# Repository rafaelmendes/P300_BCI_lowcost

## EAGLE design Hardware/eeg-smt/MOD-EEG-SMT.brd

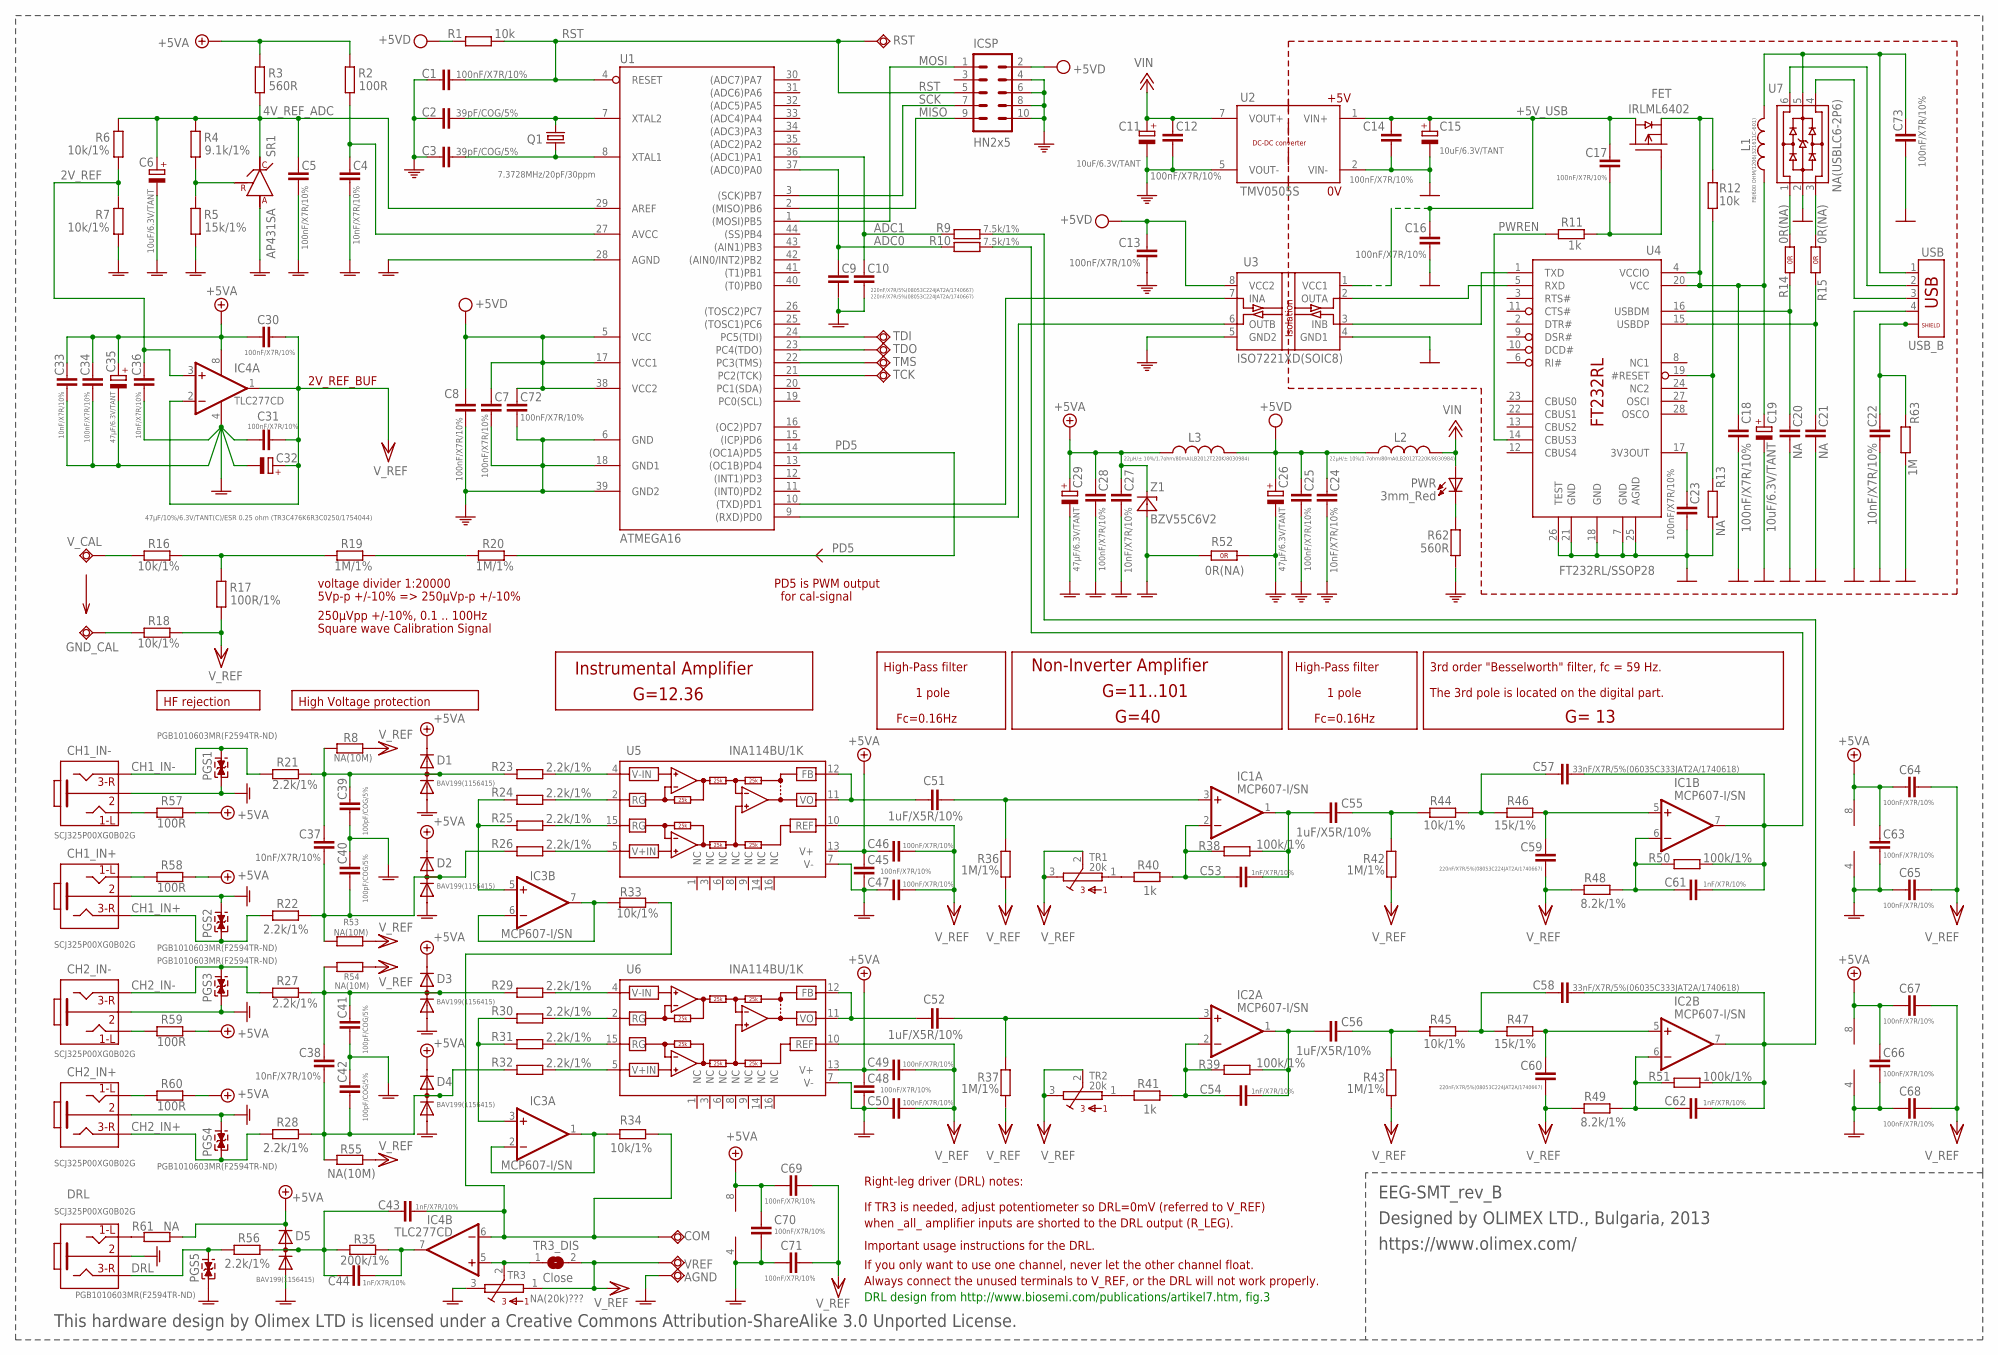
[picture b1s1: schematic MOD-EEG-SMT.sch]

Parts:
AGND: TESTPAD3; TEST_PAD40/70/SQUARE
C1, C5, C7, C8, C12, C13, C14, C16, C17, C18, C23, C25, C28, C30, C31, C34, C45, C46, C47, C48, C49, C50, C63, C64, C65, C66, C67, C68, C69, C70, C71, C72, C73: 100nF/X7R/10%; C0603_DWS
C2, C3: 39pF/COG/5%; C0603_DWS
C4, C22, C24, C27, C33, C36, C37, C38: 10nF/X7R/10%; C0603_DWS
C6, C11, C15, C19: 10uF/6.3V/TANT; CT3216
C9, C10, C59, C60: 220nF/X7R/5%(08053C224JAT2A/1740667); C0805_5MIL_DWS
C20, C21: NA; C0603_DWS_NA
C26, C29, C35: 47µF/6.3V/TANT; CT3528
C32: 47µF/10%/6.3V/TANT(C)/ESR 0.25 ohm (TR3C476K6R3C0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; CT6032
C39, C40, C41, C42: 100pF/COG/5%; C0603_DWS
C43, C44, C53, C54, C61, C62: 1nF/X7R/10%; C0603_DWS
C51, C52, C55, C56: 1uF/X5R/10%; C0603_DWS
C57, C58: 33nF/X7R/5%(06035C333JAT2A/1740618); C0603_DWS
CH1_IN+, CH1_IN-, CH2_IN+, CH2_IN-: SCJ325P00XG0B02G; PHONE_JACK-SMD
COM: TESTPAD3; TEST_PAD40/70/SQUARE
D1, D2, D3, D4, D5: BAV199(1156415); SOT23C(BAT54S)
DRL: SCJ325P00XG0B02G; PHONE_JACK-SMD
FET: IRLML6402; SOT23
GND_CAL: TESTPAD3; TEST_PAD40/70/SQUARE
IC1, IC2, IC3: MCP607-I/SN; SO08
IC4: TLC277CD; SO08
ICSP: HN2x5; ML10_NEW
L1: FB/600 OHM/1206(321611C-601); L1206_5MIL
L2, L3: 22µH/± 10%/1.7ohm/80mA(LB2012T220K/8030984); L0805_5MIL_DWS
PGS1, PGS2, PGS3, PGS4, PGS5: PGB1010603MR(F2594TR-ND); 0603
PWR: 3mm_Red; LED-3.0MM
Q1: 7.3728MHz/20pF/30ppm; HC49/SMD2_THIN
R1, R12: 10k; R0603_5MIL_DWS
R2, R57, R58, R59, R60: 100R; R0603_5MIL_DWS
R3, R62: 560R; R0603_5MIL_DWS
R4: 9.1k/1%; R0603_5MIL_DWS
R5, R46, R47: 15k/1%; R0603_5MIL_DWS
R6, R7, R16, R18, R33, R34, R44, R45: 10k/1%; R0603_5MIL_DWS
R8, R53, R54, R55: NA(10M); R0603_5MIL_DWS
R9, R10: 7.5k/1%; R0603_5MIL_DWS
R11, R40, R41: 1k; R0603_5MIL_DWS
R13, R61: NA; R0603_5MIL_DWS_NA
R14, R15, R52: 0R(NA); 0603_0R
R17: 100R/1%; R0603_5MIL_DWS
R19, R20, R36, R37, R42, R43: 1M/1%; R0603_5MIL_DWS
R21, R22, R23, R24, R25, R26, R27, R28, R29, R30, R31, R32, R56: 2.2k/1%; R0603_5MIL_DWS
R35: 200k/1%; R0603_5MIL_DWS
R38, R39, R50, R51: 100k/1%; R0603_5MIL_DWS
R48, R49: 8.2k/1%; R0603_5MIL_DWS
R63: 1M; R0603_5MIL_DWS
RST: TESTPAD80/30; SMD80/30
SR1: AP431SA; SOT-23
TCK: TESTPAD80/30; SMD80/30
TDI: TESTPAD80/30; SMD80/30
TDO: TESTPAD80/30; SMD80/30
TMS: TESTPAD80/30; SMD80/30
TR1, TR2: 20k; S64Y
TR3: NA(20k)???; S64Y
TR3_DIS: Close; SJ_1_SMALLER
U1: ATMEGA16; 44TQFP
U2: TMV0505S; TMADCDC
U3: ISO7221XD(SOIC8); SO-8_ISOLATE
U4: FT232RL/SSOP28; SSOP28
U5, U6: INA114BU/1K; SO16
U7: NA(USBLC6-2P6); USBLC6-2P6
USB: USB_B; USB_NEAR_BLACK
VREF: TESTPAD3; TEST_PAD40/70/SQUARE
V_CAL: TESTPAD3; TEST_PAD40/70/SQUARE
Z1: BZV55C6V2; MINI-MELF

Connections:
2V_REF: C36.1, IC4.3 (+IN), R6.1, R7.2
4V_REF_ADC: C5.1, C6.+, R3.1, R4.2, R6.2, SR1.1 (C), U1.29 (AREF)
+5V: C27.1, C28.1, C29.+, C30.2, C33.1, C34.1, C35.+, C45.1, C46.1, C48.1, C49.1, C63.1, C64.1, C66.1, C67.1, C69.1, C70.1, D1.2 (K), D2.2 (K), D3.2 (K), D4.2 (K), D5.2 (K), IC1.8 (V+), IC2.8 (V+), IC3.8 (V+), IC4.8 (V+), L3.2, R2.2, R3.2, R57.2, R58.2, R59.2, R60.2, R61.2, U5.13 (V+), U6.13 (V+), Z1.1 (C)
+5V_USB: C14.1, C15.+, C16.1, C17.1, FET.3 (D), U2.1 (VIN+), U3.1 (VCC1)
+12V: C11.+, C12.1, L2.1, PWR.A, U2.7 (VOUT+)
ADC0: C9.1, R10.1, U1.37 ((ADC0)PA0)
ADC1: C10.1, R9.1, U1.36 ((ADC1)PA1)
CH1_IN+: CH1_IN+.2 (3), PGS2.1, R22.1
CH1_IN-: CH1_IN-.2 (3), PGS1.2, R21.1
CH2_IN+: CH2_IN+.2 (3), PGS4.1, R28.1
CH2_IN-: CH2_IN-.2 (3), PGS3.2, R27.1
DRL: DRL.2 (3), PGS5.2, R56.1
GND: C14.2, C15.-, C16.2, C18.2, C19.-, C20.2, C21.2, C22.2, C23.2, C73.2, R13.1, R63.1, U2.2 (VIN-), U3.4 (GND1), U4.7 (GND), U4.18 (GND), U4.21 (GND), U4.25 (AGND), U4.26 (TEST), U7.2, USB.4
GNDA: AGND.P$1, C4.2, C5.2, C6.-, C9.2, C10.2, C27.2, C28.2, C29.-, C31.2, C32.-, C33.2, C34.2, C35.-, C36.2, C39.1, C40.2, C41.1, C42.2, C45.2, C47.1, C48.2, C50.1, C63.2, C65.1, C66.2, C68.1, C70.2, C71.1, CH1_IN+.1 (2), CH1_IN-.1 (2), CH2_IN+.1 (2), CH2_IN-.1 (2), D1.1 (A), D2.1 (A), D3.1 (A), D4.1 (A), D5.1 (A), DRL.1 (2), IC1.4 (V-), IC2.4 (V-), IC3.4 (V-), IC4.4 (V-), PGS1.1, PGS2.2, PGS3.1, PGS4.2, PGS5.1, R5.1, R7.1, R52.1 (1.1), SR1.3 (A), TR3.3, U1.28 (AGND), U5.7 (V-), U6.7 (V-), Z1.2 (A)
MISO: ICSP.9, U1.2 ((MISO)PB6)
MOSI: ICSP.1, U1.1 ((MOSI)PB5)
unnamed: R14.1 (1.1), U7.1
unnamed: R15.1 (1.1), U7.3
unnamed: TDI.P$1, U1.24 (PC5(TDI))
unnamed: TDO.P$1, U1.23 (PC4(TDO))
unnamed: TMS.P$1, U1.22 (PC3(TMS))
unnamed: TCK.P$1, U1.21 (PC2(TCK))
unnamed: CH1_IN-.5 (1), R57.1
unnamed: CH1_IN+.5 (1), R58.1
unnamed: C43.2, C44.2, D5.3 (AK), R35.1, R56.2
unnamed: CH2_IN+.5 (1), R60.1
unnamed: CH2_IN-.5 (1), R59.1
unnamed: DRL.5 (1), R61.1
unnamed: PWR.K (C), R62.2
unnamed: U3.2 (OUTA), U4.5 (RXD)
unnamed: C22.1, R63.2, USB.P$1 (5), USB.P$2 (6)
unnamed: U7.6, USB.2
unnamed: U3.3 (INB), U4.1 (TXD)
unnamed: C4.1, R2.1, U1.27 (AVCC)
unnamed: R4.1, R5.2, SR1.2 (R)
unnamed: U1.10 ((TXD)PD1), U3.7 (INA)
unnamed: U1.9 ((RXD)PD0), U3.6 (OUTB)
unnamed: U7.4, USB.3
unnamed: C73.1, L1.1, U7.5, USB.1
unnamed: C3.1, Q1.2, U1.8 (XTAL1)
unnamed: C2.1, Q1.1, U1.7 (XTAL2)
unnamed: R40.2, TR1.1
unnamed: R41.2, TR2.1
unnamed: R12.1, R13.2, U4.19 (#RESET)
unnamed: C23.1, U4.17 (3V3OUT)
unnamed: C18.1, C19.+, FET.2 (S), L1.2, R12.2, U4.4 (VCCIO), U4.20 (VCC)
unnamed: C55.2, R42.1, R44.1
unnamed: C51.1, U5.11 (VO), U5.12 (FB)
unnamed: R23.1, U5.4 (V-IN)
unnamed: R24.1, U5.2 (RG)
unnamed: C37.1, C40.1, D2.3 (AK), R22.2, R26.2, R53.2
unnamed: C37.2, C39.2, D1.3 (AK), R8.2, R21.2, R23.2
unnamed: C38.1, C42.1, D4.3 (AK), R28.2, R32.2, R55.2
unnamed: C38.2, C41.2, D3.3 (AK), R27.2, R29.2, R54.2
unnamed: R25.1, U5.15 (RG)
unnamed: C51.2, IC1.3 (+IN), R36.1
unnamed: IC3.5 (+IN), R24.2, R25.2
unnamed: C53.2, C55.1, IC1.1 (OUT), R38.2
unnamed: C53.1, IC1.2 (-IN), R38.1, R40.1
unnamed: R26.1, U5.5 (V+IN)
unnamed: C59.1, IC1.5 (+IN), R46.2
unnamed: C57.1, R44.2, R46.1
unnamed: C57.2, C61.2, IC1.7 (OUT), R10.2, R50.2
unnamed: C61.1, IC1.6 (-IN), R48.1, R50.1
unnamed: C52.2, IC2.3 (+IN), R37.1
unnamed: C54.2, C56.1, IC2.1 (OUT), R39.2
unnamed: C54.1, IC2.2 (-IN), R39.1, R41.1
unnamed: C60.1, IC2.5 (+IN), R47.2
unnamed: C58.1, R45.2, R47.1
unnamed: C58.2, C62.2, IC2.7 (OUT), R9.2, R51.2
unnamed: C62.1, IC2.6 (-IN), R49.1, R51.1
unnamed: C56.2, R43.1, R45.1
unnamed: C52.1, U6.11 (VO), U6.12 (FB)
unnamed: R30.1, U6.2 (RG)
unnamed: R31.1, U6.15 (RG)
unnamed: IC3.3 (+IN), R30.2, R31.2
unnamed: R29.1, U6.4 (V-IN)
unnamed: R32.1, U6.5 (V+IN)
unnamed: IC3.1 (OUT), IC3.2 (-IN), R34.2
unnamed: IC3.6 (-IN), IC3.7 (OUT), R33.2
unnamed: IC4.5 (+IN), TR3.2, TR3_DIS.1
unnamed: C44.1, IC4.7 (OUT), R35.2
unnamed: R19.2, R20.1
unnamed: C43.1, COM.P$1, IC4.6 (-IN), R33.1, R34.1
unnamed: R16.2, R17.2, R19.1
unnamed: R16.1, V_CAL.P$1
unnamed: GND_CAL.P$1, R18.1
unnamed: C17.2, FET.1 (G), R11.2
PD5: R20.2, U1.14 ((OC1A)PD5)
PE: C1.2, C2.2, C3.2, C7.2, C8.2, C11.-, C12.2, C13.2, C24.2, C25.2, C26.-, C72.2, ICSP.4, ICSP.6, ICSP.8, ICSP.10, R52.2 (1.2), R62.1, U1.6 (GND), U1.18 (GND1), U1.39 (GND2), U2.5 (VOUT-), U3.5 (GND2)
PWREN: R11.1, U4.14 (CBUS3)
RST: C1.1, ICSP.5, R1.2, RST.P$1, U1.4 (RESET)
SCK: ICSP.7, U1.3 ((SCK)PB7)
USBDM: C20.1, R14.2 (1.2), U4.16 (USBDM)
USBDP: C21.1, R15.2 (1.2), U4.15 (USBDP)
VCC/2: C30.1, C31.1, C32.+, C46.2, C47.2, C49.2, C50.2, C59.2, C60.2, C64.2, C65.2, C67.2, C68.2, C69.2, C71.2, IC4.1 (OUT), IC4.2 (-IN), R8.1, R17.1, R18.2, R36.2, R37.2, R42.2, R43.2, R48.2, R49.2, R53.1, R54.1, R55.1, TR1.2, TR1.3, TR2.2, TR2.3, TR3.1, TR3_DIS.2, U5.10 (REF), U6.10 (REF), VREF.P$1
VPP: C7.1, C8.1, C13.1, C24.1, C25.1, C26.+, C72.1, ICSP.2, L2.2, L3.1, R1.1, U1.5 (VCC), U1.17 (VCC1), U1.38 (VCC2), U3.8 (VCC2)

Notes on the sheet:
PD5 is PWM output
for cal-signal
250µVpp +/-10%, 0.1 .. 100Hz
Square wave Calibration Signal
voltage divider 1:20000
G=40
G=11..101
5Vp-p +/-10% => 250µVp-p +/-10%
3rd order "Besselworth" filter, fc = 59 Hz.
The 3rd pole is located on the digital part.
Fc=0.16Hz
HF rejection
High Voltage protection
High-Pass filter
Non-Inverter Amplifier
G= 13
1 pole
G=12.36
2V_REF_BUF
Instrumental Amplifier
DRL design from http://www.biosemi.com/publications/artikel7.htm, fig.3
If TR3 is needed, adjust potentiometer so DRL=0mV (referred to V_REF)
when _all_ amplifier inputs are shorted to the DRL output (R_LEG).
If you only want to use one channel, never let the other channel float.
Important usage instructions for the DRL.
Always connect the unused terminals to V_REF, or the DRL will not work properly.
Right-leg driver (DRL) notes:
+5V
This hardware design by Olimex LTD is licensed under a Creative Commons Attribution-ShareAlike 3.0 Unported License.
Designed by OLIMEX LTD., Bulgaria, 2013
https://www.olimex.com/
EEG-SMT_rev_B

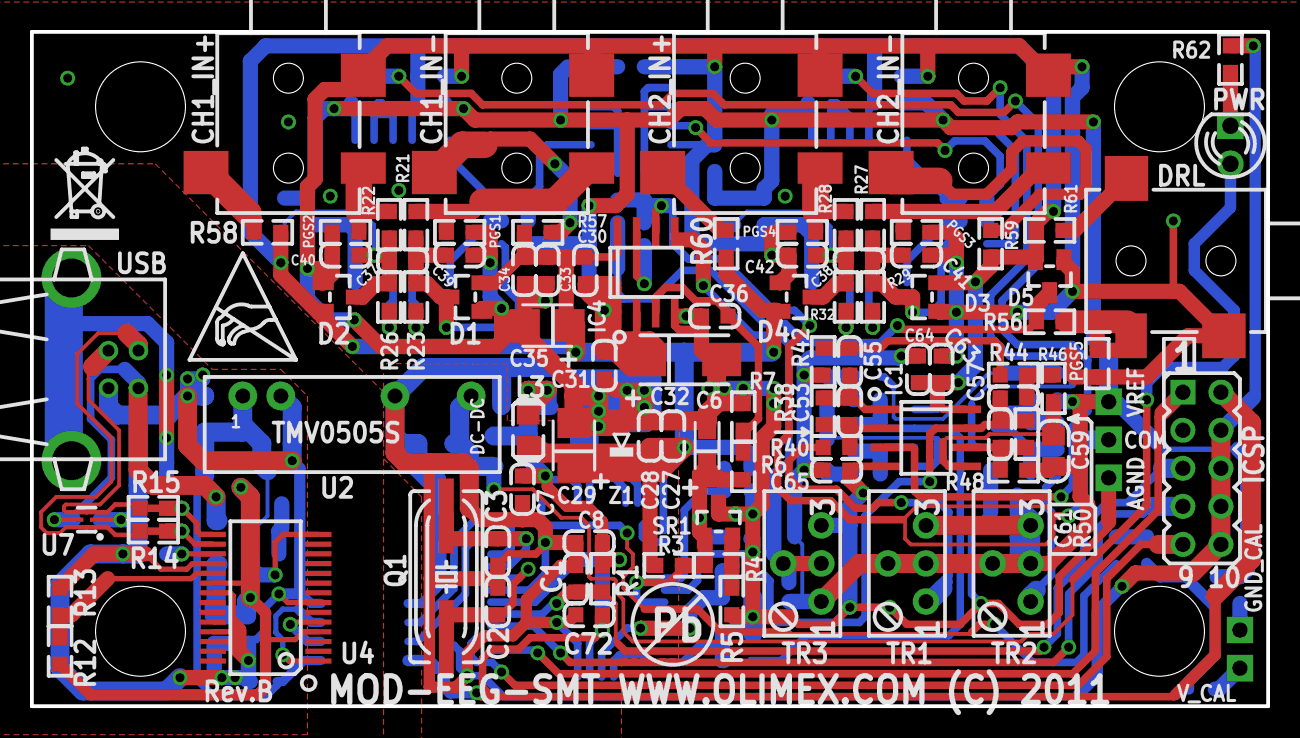
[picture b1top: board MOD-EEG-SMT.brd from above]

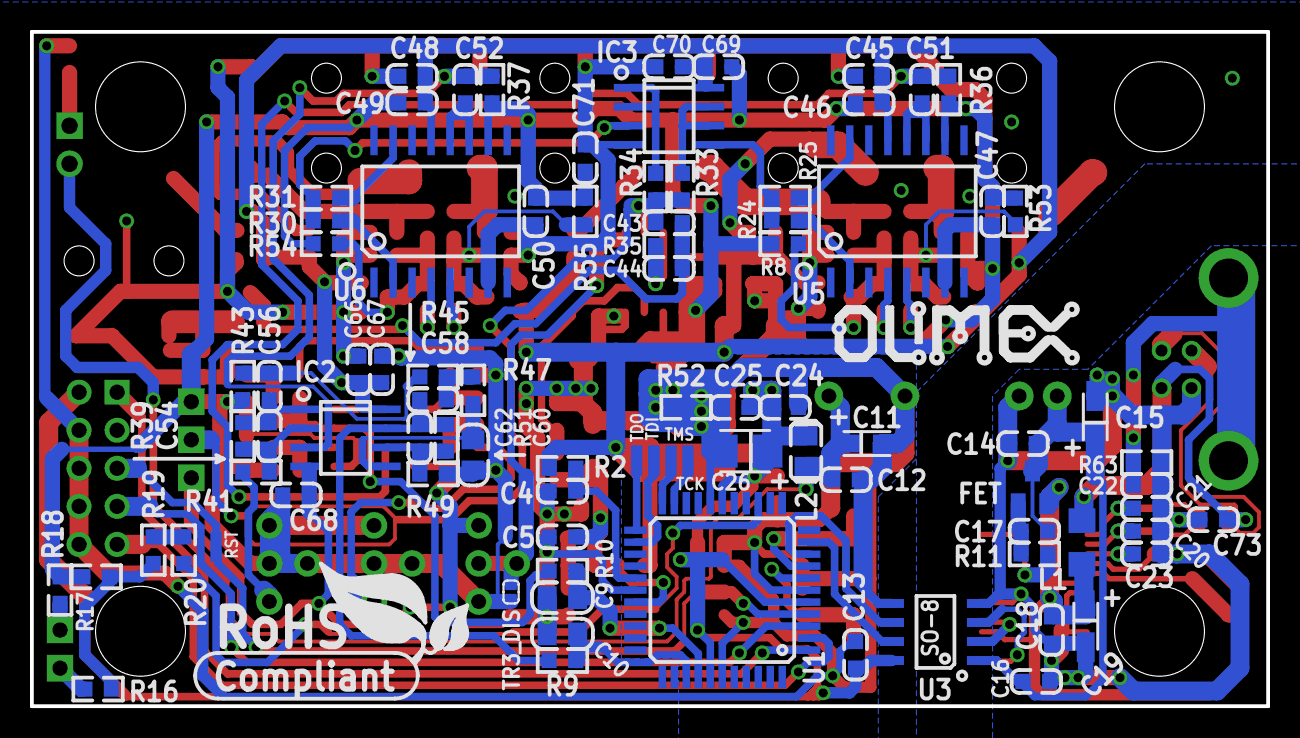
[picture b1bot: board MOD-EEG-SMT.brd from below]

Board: 2 copper layers, 82.5 x 45.0 mm, 191 parts (90 on the bottom side), 97 nets.

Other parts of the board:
U$1: ESD_SYMBOL
U$2: OLIMEX1_V
U$3: PB
U$4: RECYCLE_BIN1/8
U$11: ROHS

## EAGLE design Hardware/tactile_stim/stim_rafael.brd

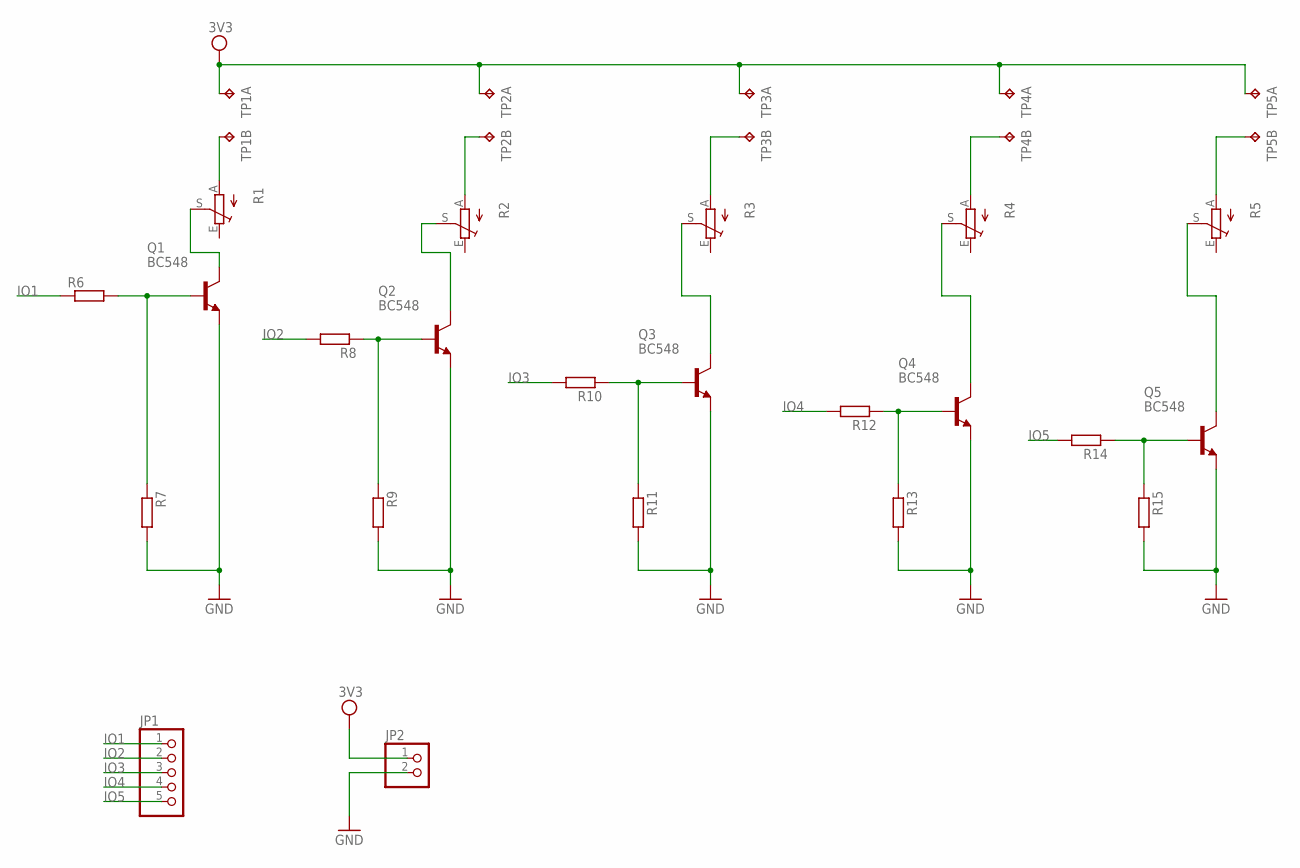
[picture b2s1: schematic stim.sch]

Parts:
JP1: PINHD-1X5; 1X05
JP2: PINHD-1X2; 1X02
Q1, Q2, Q3, Q4, Q5: BC548; TO92-EBC
R1, R2, R3, R4, R5: TRIM_EU-B25V; B25V
R6, R7, R8, R9, R10, R11, R12, R13, R14, R15: RR1206; R1206
TP1, TP2, TP3, TP4, TP5: TP2P2-38-17; P2-38-17

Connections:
GND: JP2.2, Q1.E, Q2.E, Q3.E, Q4.E, Q5.E, R7.2, R9.2, R11.2, R13.2, R15.2
IO1: JP1.1, R6.1
IO2: JP1.2, R8.2
IO3: JP1.3, R10.2
IO4: JP1.4, R12.2
IO5: JP1.5, R14.2
unnamed: R2.A, TP2.TP-2
unnamed: R3.A, TP3.TP-2
unnamed: Q3.C, R3.S
unnamed: Q1.C, R1.S
unnamed: Q5.B, R14.1, R15.1
unnamed: R1.A, TP1.TP-2
unnamed: R4.A, TP4.TP-2
unnamed: Q4.C, R4.S
unnamed: R5.A, TP5.TP-2
unnamed: Q5.C, R5.S
unnamed: Q4.B, R12.1, R13.1
unnamed: Q3.B, R10.1, R11.1
unnamed: Q2.B, R8.1, R9.1
unnamed: Q1.B, R6.2, R7.1
SDA: Q2.C, R2.S
VDD: JP2.1, TP1.TP-1, TP2.TP-1, TP3.TP-1, TP4.TP-1, TP5.TP-1

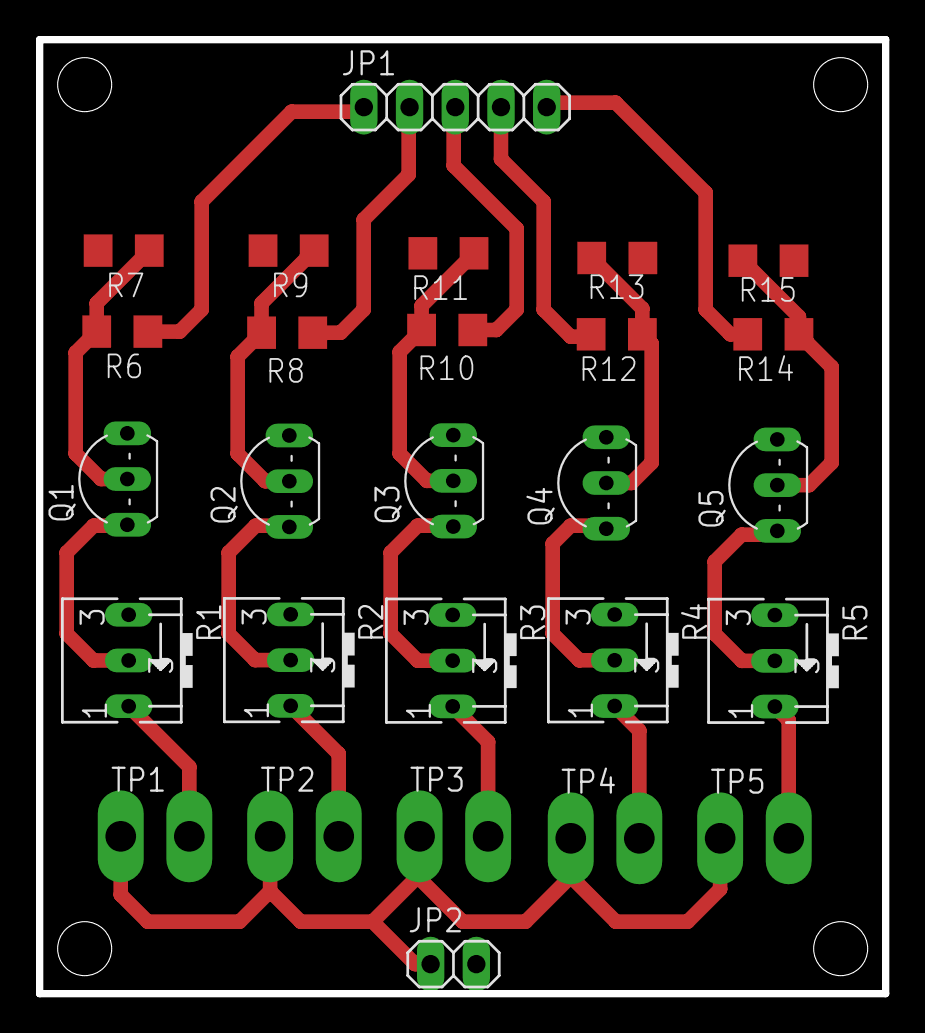
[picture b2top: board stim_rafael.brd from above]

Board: 2 copper layers, 47.0 x 53.0 mm, 27 parts (0 on the bottom side), 22 nets.

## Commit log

2016-02-17 first commit; imported from bitbucket

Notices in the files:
Hardware/eeg-smt/MOD-EEG-SMT.brd:
MOD-EEG-SMT WWW.OLIMEX.COM (C) 2011
